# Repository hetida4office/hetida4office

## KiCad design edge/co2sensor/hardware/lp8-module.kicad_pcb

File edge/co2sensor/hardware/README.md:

# EasyEDA sources for Schematic and PCB

How to use：
* Go to EasyEDA home page.
* Log in
* Select "Document" > "Open" > "EasyEDA Source".
* Upload the json files in this folder.

# Fab files
* The files in the 'fab/' subfolder can be used to produce the current version of the hardware at any fab house.

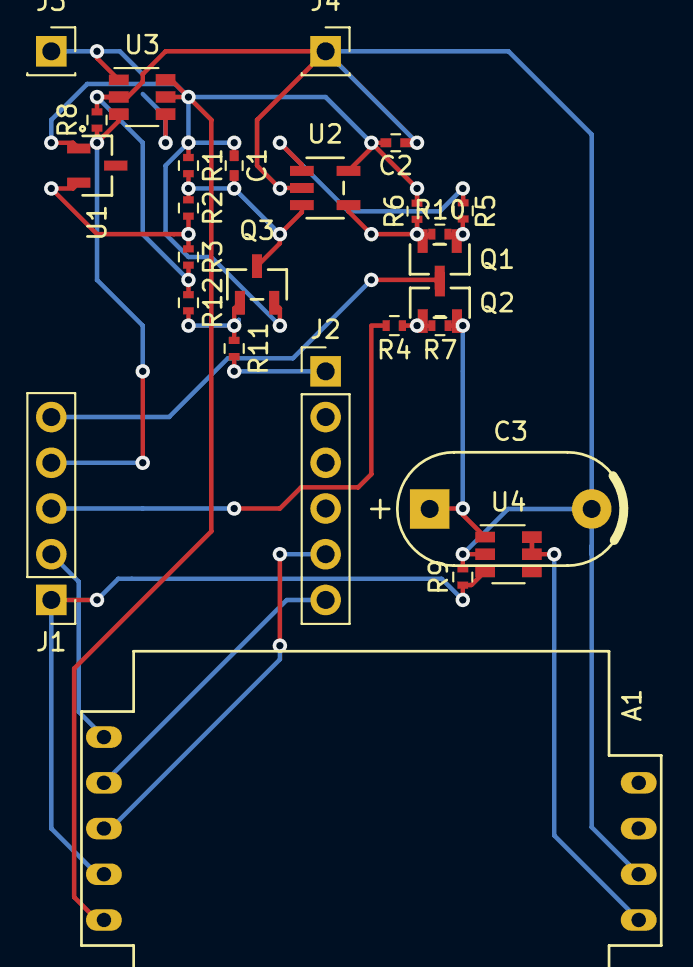
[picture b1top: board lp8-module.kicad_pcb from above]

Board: 2 copper layers, 28 parts (1 on the bottom side), 21 nets.

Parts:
A1: SenseAir-LP8; LP8
C1: 100n; C_0402
C2: 10n; C_0402
C3: 470m; AVX_SCM_L14.00_W6.30
C4: 470p; C_0402
J1: Conn_01x05_Male; PinHeader_1x05_P2.54mm_Vertical
J2: Conn_01x06_Male; PinHeader_1x06_P2.54mm_Vertical
J3, J4: Conn_01x01_Male; PinSocket_1x01_P2.54mm_Vertical
Q1, Q2, Q3: PMOS-SI2315BDS-T1-E3; SI2315BDS-T1-E3
R1: 82k; R_0402
R2: 910k; R_0402
R3: 249k; R_0402
R4, R5, R11: 1k1; R_0402
R6: 500m; R_0402
R7, R8, R9, R10, R12: 100k; R_0402
U1: MAX6006/LT1634; 21-0051H
U2: MCP6041T-EOT; MCP6041T-E&slash_OT
U3, U4: TPS22917; SOT-23-6

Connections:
/3V3: C4.1, J3.1, U3.1
/LP8/LP8_3V3: A1.2.1, C1.1, C2.2, Q3.2, R1.1, R6.1, U1.1, U2.5, U3.5, U3.6
/LP8/V+: C1.2, Q3.3, R1.2, R2.1, U2.3
/LP8/V-: Q1.2, R6.2, R10.1, U2.4
/LP8_EN_CHARGE: J2.1, R11.2
/LP8_EN_MEAS: A1.2.2, J1.1, R9.1, U4.3
/LP8_EN_PWR: J1.4, R8.2, U3.3
/LP8_EN_REV_BLOCK: J1.3, R4.2
/LP8_MEAS_RDY: A1.2.5, J1.2
/LP8_VCAP: J1.5, Q1.3, Q2.3
/RxD: A1.2.4, J2.6
/TxD: A1.2.3, J2.5
GND: A1.1.2, C2.1, C3.2, J4.1, R3.2, R8.1, R9.2, R12.1, U2.2, U3.2, U4.2
unnamed: A1.1.1, U4.5, U4.6
unnamed: C3.1, Q2.2, R7.1, U4.1
unnamed: C4.2, U3.4
unnamed: Q1.1, R5.1, R10.2
unnamed: Q2.1, R4.1, R7.2
unnamed: Q3.1, R11.1, R12.2
unnamed: R2.2, R3.1, U1.2
unnamed: R5.2, U2.1

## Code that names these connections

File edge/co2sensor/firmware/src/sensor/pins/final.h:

#ifndef PINS_H
#define PINS_H

#include "hal/nrf_gpio.h"
#include <nrfx_lpcomp.h>

// Custom Board
#define PIN_LED1 NRF_GPIO_PIN_MAP(0, 30)
#define PIN_LED2 NRF_GPIO_PIN_MAP(0, 31)
#define PIN_SWITCH NRF_GPIO_PIN_MAP(0, 10)

// UART
#define PIN_UART_RX NRF_GPIO_PIN_MAP(0, 5)
#define PIN_UART_TX NRF_GPIO_PIN_MAP(1, 9)

// LP8
#define PIN_LP8_EN_CHARGE NRF_GPIO_PIN_MAP(0, 9) // digital out, D0S1, no pull
#define PIN_LP8_EN_REV_BLOCK NRF_GPIO_PIN_MAP(0, 3) // digital out, S0D1, no pull
#define PIN_LP8_EN_PWR NRF_GPIO_PIN_MAP(1, 13) // digital out, D0S1, no pull
#define PIN_LP8_EN_MEAS NRF_GPIO_PIN_MAP(1, 11) // digital out, D0S1, no pull
#define PIN_LP8_VCAP_LPCOMP NRF_LPCOMP_INPUT_0 // analog in
#define PIN_LP8_MEAS_RDY NRF_GPIO_PIN_MAP(1, 10) // digital in
#define PIN_LP8_RXD PIN_UART_TX // UART
#define PIN_LP8_TXD PIN_UART_RX // UART

// I2C
#define PIN_I2C_SDA NRF_GPIO_PIN_MAP(0, 13)
#define PIN_I2C_SCL NRF_GPIO_PIN_MAP(0, 24)

// BAT
#define PIN_BAT_nEN_MEAS NRF_GPIO_PIN_MAP(0, 29) // digital out, S0D1, no pull
#define PIN_BAT_MEAS_SAADC NRF_SAADC_INPUT_AIN4 // analog in

#define NUM_DIGITAL_IN 1 // required to configure resources for GPIOTE event listeners

#endif // PINS_H

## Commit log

2020-12-30 latest fab files
2021-01-01 formatting
2021-01-01 add second sensor
2021-01-01 bump version
2021-01-01 persistent volume for grafana
2021-01-01 move sensor name to header
2021-01-02 sensor specific MQTT client id and fix for failed messages
2021-01-06 handle invalid topic id error
2021-01-09 let thread/mqtt sleep between measurements
2021-01-10 add missing disconnection/sleep timeout
2021-02-13 implement lp8 error reporting
2021-02-13 format/simplify firmware main
2021-02-13 fix disconnection race
2021-02-13 code formatting, removing redundant dependencies
2021-02-13 support final hardware
2021-02-13 revert unwanted changes to flyway scripts
2021-02-23 update image
2021-03-03 add current hardware files
